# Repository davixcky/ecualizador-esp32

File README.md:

# Ecualizador de audio de tres bandas con ESP32

## Prototipo en protoboard

[Guía de montaje y esquema (PDF)](docs/protoboard/guia-prototipo-protoboard.pdf) · [Lista de materiales (CSV)](docs/protoboard/materiales.csv) · [Conexiones pin por pin (CSV)](docs/protoboard/conexiones.csv). Incluye pruebas con generador y osciloscopio, y ampliación con ESP32, pantalla y NeoPixel. [Fuente LaTeX](docs/latex/prototipo-protoboard.tex).

## Modelo mecánico vigente E.5

[Vista cerrada](hardware/E5-perforadas/3d/ecualizador-E5-cerrado.png) ·
[vista abierta](hardware/E5-perforadas/3d/ecualizador-E5-abierto.png) ·
[planta desplegada](hardware/E5-perforadas/3d/ecualizador-E5-planta.png) ·
[soporte de pantalla](hardware/E5-perforadas/3d/ecualizador-E5-pantalla-soporte-explotado.png) ·
[cómo regenerar](hardware/E5-perforadas/3d/README.md) ·
[prácticas propias de E.5](hardware/E5-perforadas/3d/BEST-PRACTICES.md).
Estas imágenes fijas son la referencia visual del CAD vigente: tapa magnética, piezas por encastre,
cinco controles rotativos, pantalla ESP32-3248S035 de 3,5" recibida (en vertical) y cuatro tarjetas perforadas.

El [video de 50 segundos](docs/video/ecualizador-animado.mp4) se conserva como material histórico.
Su [revisión](docs/video/REVIEW.md) documenta que el interior quedó anterior a los encastres actuales;
no debe usarse como guía de fabricación o montaje.

> **Controles vigentes:** no hay potenciómetros deslizables. Los informes y la presentación de la Fase 2 (`docs/latex/`, `docs/informe-fase2.*`, `docs/presentacion/`) y la carpeta [`cad/`](cad/LEEME-ARCHIVO.md) describen la revisión D.2 archivada, que sí los dibujaba; no representan el hardware que se va a montar. Las compras respaldadas están en [`hardware/COMPONENTES-COMPRADOS-VERIFICADOS.md`](hardware/COMPONENTES-COMPRADOS-VERIFICADOS.md).

Proyecto de Electrónica II · Universidad de la Costa · Leo Rojas, David Orozco y Manuel Castilla.

La ruta de audio usa filtros activos y controles analógicos. El firmware existente lee los niveles y dibuja una FFT para la pantalla Waveshare de **1,9 pulgadas, 170 × 320, ST7789V2**. El CAD vigente (2026-11-24) la sustituye por la **ESP32-3248S035 recibida** (TFT táctil ST7796 de 3,5 pulgadas, 320 × 480, en vertical; ya funciona con `firmware-cyd`), enlazada por **ESP-NOW** (solo recibe +5 V y GND por cable), y cambia el ESP32S de 38 pines por un **ESP32 DevKit V1 de 30 pines** (sin comprar). [`firmware-lilygo/`](firmware-lilygo/) contiene el simulador visual de la T4-S3 descartada (queda como referencia; no corresponde al CAD vigente). El gabinete E.5 mide 278 × 192 × 64 mm, usa cierre magnético y tres barras de luz (12 píxeles lógicos); el gabinete EQ / 03 con imanes de la Fase 2 quedó archivado.

| Entrega | Archivos actuales |
|---|---|
| Presentación en LaTeX | [PDF](docs/presentacion/presentacion-fase2.pdf) · [PowerPoint con notas](docs/presentacion/presentacion-fase2.pptx) · [PDF con notas](docs/presentacion/presentacion-notas.pdf) |
| Exposición con animaciones | [PowerPoint animado](docs/presentacion/presentacion-animada.pptx) · [PDF por pasos](docs/presentacion/presentacion-animada.pdf) · [Cómo presentar](docs/presentacion/LEEME.md) |
| Informe | [PDF](docs/informe-fase2.pdf) · [Word](docs/informe-fase2.docx) · [Markdown](docs/informe-fase2.md) |
| Fuentes editables en LaTeX | [Informe](docs/latex/informe.tex) · [Presentación Beamer](docs/latex/presentacion.tex) |
| Presentación corta de filtros | [PDF de 10 diapositivas](docs/presentacion/presentacion-filtros-hoy.pdf) · [PowerPoint con notas](docs/presentacion/presentacion-filtros-hoy.pptx) · [Fuente LaTeX](docs/latex/presentacion-filtros.tex) |
| Ensayo de hoy | [Generador y osciloscopio: guía](simulacion/velxio/DEMO-HOY.md) |
| Paquete para otro computador | [ZIP portátil: presentación, esquema y simulaciones](docs/exposicion-portable.zip) |
| Simulación en Velxio | [Abrir casos locales](simulacion/velxio/index.html) · [Instrucciones y alcance](simulacion/velxio/README.md) · [100 Hz](simulacion/velxio/filtros-100Hz.vlx) · [1 kHz](simulacion/velxio/filtros-1000Hz.vlx) · [8 kHz](simulacion/velxio/filtros-8000Hz.vlx) |
| Proyecto único E.4-LM324 | [Abrir en KiCad](hardware/E4-LM324/proyecto/ecualizador-E4-LM324.kicad_pro) · [Esquema PDF](hardware/E4-LM324/proyecto/ecualizador-E4-LM324.pdf) · [Fabricación](hardware/E4-LM324/fabricacion/) · [Vista superior](hardware/E4-LM324/vistas/3d-top.png) · [Vista inferior](hardware/E4-LM324/vistas/3d-bottom.png) · [Montaje](hardware/E4-LM324/README.md) |
| Prototipo modular E.5 en tarjetas perforadas | [Esquema modular PDF](hardware/E5-perforadas/esquema-modular-perforadas.pdf) · [Proyecto KiCad](hardware/E5-perforadas/proyecto/ecualizador-perforadas.kicad_pro) · [Conexiones](hardware/E5-perforadas/conexiones-entre-tarjetas.csv) · [Modelo 3D editable](hardware/E5-perforadas/3d/ecualizador-E5-perforadas.FCStd) · [Vista cerrada](hardware/E5-perforadas/3d/ecualizador-E5-cerrado.png) · [Vista abierta](hardware/E5-perforadas/3d/ecualizador-E5-abierto.png) · [Planta desplegada](hardware/E5-perforadas/3d/ecualizador-E5-planta.png) · [Modelo 3D: cómo regenerar](hardware/E5-perforadas/3d/README.md) · [Guía](hardware/E5-perforadas/README.md) |
| PCB E.3-LM324 de una cara | [KiCad](hardware/E3-LM324/placa/ecualizador-E3-LM324.kicad_pcb) · [Fabricación](hardware/E3-LM324/fabricacion/) · [Vista superior](hardware/E3-LM324/vistas/3d-top.png) · [Vista inferior](hardware/E3-LM324/vistas/3d-bottom.png) · [Reglas y montaje](hardware/E3-LM324/README.md) |
| PCB de una cara D.2 (anterior, MCP6004) | [Plano PDF](hardware/pcb-rev-D2.pdf) · [KiCad](hardware/ecualizador.kicad_pcb) · [DRC](hardware/drc.rpt) · [Montaje y puentes](hardware/una-cara/LEEME.md) · [BOM](hardware/fabricacion/bom.csv) |
| Modelos 3D | [Gabinete STEP](cad/ecualizador-gabinete.step) · [Piezas STL](cad/stl/) · [Retrofit D.3 STEP](hardware/3d/ecualizador-D3-retrofit.step) · [Vista superior](hardware/3d/ecualizador-D3-retrofit.png) · [Vista inferior](hardware/3d/ecualizador-D3-retrofit-inferior.png) · [PCB D.2 STEP](hardware/3d/ecualizador-placa.step) |
| Propuesta original y rúbrica | [Fase 1](docs/fase1/) |

## Estado de la revisión del 5 de noviembre de 2026

- **Actualización del 24 de noviembre de 2026:** la pantalla pasa de la LilyGO T4-S3 a la **ESP32-3248S035 de 3,5 pulgadas RECIBIDA** (la publicación anunciaba una de 2,8): montada en vertical, ST7796 confirmado y la interfaz de `firmware-cyd` ya corre en ella con vistas de bandas y espectro. Los datos viajarán por **ESP-NOW** (decisión del usuario); el arnés queda en +5 V/GND. El ESP32 del montaje pasa a un DevKit V1 de 30 pines (sin comprar; pines verificados compatibles). El modelo 3D E.5, sus 13 probetas y las camas de impresión reflejan la pantalla de 3,5; el video y el esquema eléctrico siguen mostrando revisiones anteriores.
- E.4-LM324 es la fuente única de fabricación: esquema físico y PCB en el mismo proyecto, paridad estricta KiCad con 0 diferencias, ERC con 0 errores y DRC con 0 errores/0 conexiones abiertas. Los 23 avisos ERC son exclusivamente pines `NC-*` intencionales.
- D.3 usa cuatro LM324N a 5 V, conserva VREF en 1,65 V y protege las cuatro entradas ADC con atenuadores 2:1 referidos a VREF. El firmware reconstruye la amplitud original.
- ngspice: 25 casos del diseño revisado cumplen; el caso histórico de Fase 1 se conserva deliberadamente como no conforme. El modelo funcional del LM324 valida margen de modo común, dinámica y protección ADC, pero no sustituye mediciones físicas.
- La PCB D.2 archivada conserva el ruteo y BOM del MCP6004 a 3,3 V. No coincide directamente con D.3: para reutilizarla se debe seguir la [adaptación LM324](hardware/RETROFIT-LM324.md). No enviar D.2 a fabricar como si ya incorporara R33–R40.
- La nueva PCB [E.3-LM324](hardware/E3-LM324/README.md) incorpora LM324 a 5 V y R33–R40: una cara, 23 alambres, pistas de 0,7 mm o más, donas de 1,9 mm o más y ninguna pista de paso entre pines a 2,54 mm. DRC sin errores ni conexiones abiertas; montaje físico pendiente.
- E.4 sustituye a E.3 como opción recomendada para soldadura manual: pads de componentes ovalados de al menos 2,4 × 2,0 mm, pads propios de puente de 2,4 mm, 25 alambres de hasta 30,9 mm, alimentación +5 V perimetral y ningún puente reutiliza un agujero de componente.
- Velxio: tres proyectos ejecutados con motor SPICE; predominan graves a 100 Hz, medios a 1 kHz y agudos a 8 kHz. Los filtros usan operacionales ideales. Un cuarto [ensayo animado de 12 NeoPixel](simulacion/velxio/led-animado.vlx) ejecuta código del ESP32; usa un patrón programado sin audio.
- Velxio integrado: entrada → filtros → detectores → ADC ESP32 → TFT ILI9341, usando QEMU. Se comprueba el predominio de cada banda con 100 Hz, 1 kHz y 8 kHz. FFT sin calibración de frecuencia; no incluye potencia ni adaptación LED. [Guía y modelos](simulacion/velxio/INTEGRADO.md).
- Firmware: compilación ESP32 correcta; 19 comprobaciones DSP y cinco comparaciones de dibujo por franjas correctas en el computador.
- El montaje físico, las mediciones con instrumentos y el requisito de más del 70 % de dispositivos adquiridos y conectados **siguen sin evidencia en este repositorio**.

Los [resultados ngspice vigentes](simulacion/resultados.md) corresponden a D.3-LM324; `docs/validacion/` conserva registros históricos de D.2. Los renders provienen del CAD y de KiCad; las pantallas se dibujan con el código de interfaz y datos de ejemplo.

## Pantalla e iluminación

J4 es un adaptador de ocho señales a 2,54 mm, no la huella GH1.25 de Waveshare. Conectar por **nombre de señal**, siguiendo la tabla del informe: VCC, GND, DIN, CLK, CS, DC, RST y BL. La interfaz trabaja en horizontal a 320 × 170.

GPIO25 controla la tira mediante un 74AHCT125 y 330 Ω. J5 lleva 5 V, DIN y GND. Se prevén dos tramos de 100 mm, seis LED por tramo, y canales de 102 × 10,6 × 3 mm con difusores. El brillo inicial es 32/255, fijo. La fuente prevista es de 5 V / 3 A por J6; **desconectar VBUS del USB cuando se usa esa fuente**. No alimentar los LED desde 3,3 V ni usar VREF como retorno.

## Reproducir los archivos

Los PDF usan el logo oficial CUC, rojo institucional y Red Hat Display, según el [manual consultado](img/marca/README.md). Las fuentes vigentes son los `.tex` (LuaLaTeX). El PowerPoint contiene imágenes de las diapositivas y notas; el texto se edita en LaTeX. El HTML anterior está archivado en `docs/archivo/`.

```sh
# TeX Live: latex-extra, lang-spanish, fonts-recommended, luatex; pandoc
# Python: pymupdf, python-pptx (para exportar PNG y PowerPoint)
bash herramientas/compilar_documentos.sh

# Firmware y pruebas en computador
pio run -d firmware
make -C firmware/test prueba pantallas

# Conectividad y simulación (ngspice, numpy, matplotlib)
python3 herramientas/verificar_netlist.py
.venv/bin/python herramientas/simulacion.py

# PCB de una cara: regenerar el esquema físico E.4 y verificar
python3 herramientas/generar_esquematico_e4.py
kicad-cli pcb drc --schematic-parity hardware/E4-LM324/proyecto/ecualizador-E4-LM324.kicad_pcb
python3 herramientas/validar_pcb_cnc.py hardware/E4-LM324/proyecto/ecualizador-E4-LM324.kicad_pcb 0.7 1.9

# CAD (CadQuery) y renders (Blender, KiCad)
.venv/bin/python herramientas/validar_cad.py
bash cad/generar.sh

# Repetir la comprobación web (Node y Playwright con Chromium)
node herramientas/validar_velxio.cjs
node herramientas/validar_led_velxio.cjs
```

Las vistas de ensamblaje y colores de bandas parten de C2-ABPR; la revisión EQ / 03 adopta acabado grafito, rotulación compacta y cierre magnético. Las cotas de pantalla, controles y conectores deben contrastarse con las piezas adquiridas antes de imprimir y montar.

La presentación incluye fragmentos del esquema real para explicar preamplificador, Sallen-Key, sumador y detector. Los PDF adjuntan el esquema, el plano D.2 y los proyectos Velxio. El enlace y el QR abren el editor; después se importa el caso `.vlx`. Ver [cierre magnético y cotas](cad/CIERRE-MAGNETICO.md).

La PCB D.2 organiza las etapas con el flujo Python/KiCad y Freerouting de medidor-energia-esp32: ESP32 a la derecha, operacionales por etapas y cableado identificado por colores. Usa una sola cara de cobre y puentes aislados. Los controles van en el panel y requieren las [cabeceras y cables de montaje](hardware/una-cara/LEEME.md). Los Gerbers de dos capas B.1 están archivados y no corresponden al montaje vigente.

### Placa única E.2 (propuesta, 33 alambres)

[E.2](hardware/E2-placa-unica/README.md) reduce los 80 tramos de D.2 a 33 alambres en una sola placa de una cara de 200 × 120 mm para el gabinete original. Usa plano de GND, componentes con las patas más abiertas para pasar pistas por debajo, y reasigna las secciones de los amplificadores y los GPIO. El firmware se compila con `pio run -e e2`. La alternativa de tres placas está en [E.1](hardware/E1-tres-placas/README.md).

### Montaje de los puentes

La cara superior lleva 29 puentes cortos (hasta 20 mm entre extremos). Los 51 cables restantes se montan aislados por debajo. El total sigue siendo 80 tramos; no se añade una capa de cobre. [La guía](hardware/PUENTES.md) y [el plano de cuatro páginas](hardware/pcb-rev-D2.pdf) indican la cara de cada conexión. Los arcos del render son orientativos: el montaje requiere comprobar separación, sujeción y continuidad.

### Prototipo de laboratorio con TL072CP (±12 V)

Para el montaje con los integrados disponibles: [guía PDF](docs/prototipo-tl072/guia-prototipo-TL072.pdf), [fuente LaTeX](docs/latex/prototipo-tl072.tex) y [paquete de conexiones y simulación](docs/prototipo-tl072/prototipo-TL072.zip). Utiliza cuatro TL072, salida de línea y medidas a 100 Hz, 1 kHz y 8 kHz. Es una variante analógica independiente del diseño MCP6004 de 3,3 V; sus salidas no se conectan directamente al ESP32.

Esquema completo del prototipo en una lámina A2: [PDF](docs/prototipo-tl072/esquema-completo-TL072.pdf) · [SVG editable](docs/prototipo-tl072/esquema-completo.svg). Incluido al final de la guía TL072.

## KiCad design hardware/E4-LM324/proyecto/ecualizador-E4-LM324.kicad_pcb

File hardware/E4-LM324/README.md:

# E.4-LM324 · una cara para soldadura manual

E.4 conserva el circuito validado D.3-LM324 y la topología de una sola cara, pero revisa la geometría pensando en fresado CNC y montaje con cautín. Es la revisión recomendada frente a E.3.

## Cambios para facilitar el montaje

- Todos los pads de componentes tienen al menos **2,4 × 2,0 mm**. En piezas sin restricción de paso, 132 pads son de 2,4 mm o mayores en ambos ejes.
- Los 44 pads propios de puentes son circulares de **2,4 mm**, con taladro de 0,8 mm.
- **Ningún puente reutiliza el agujero de un componente.** Cada extremo termina en un pad perforado propio; la comprobación automática aparece como `shared_bridge_holes: []`.
- El taladro propio de JP19 queda bajo el cuerpo de R25 por la isla de masa aislada de esa zona. Se suelda JP19 antes de montar R25; el agujero sigue siendo independiente de los dos pads de R25.
- El enlace largo de +5 V se sustituyó por una pista perimetral de 1,0 mm.
- No quedan ramales de cobre sueltos.

## Resultado verificado

| Regla | Resultado |
|---|---:|
| Cobre | solo B.Cu |
| Pista de señal mínima | 0,7 mm |
| Alimentación | 1,0 mm |
| Pad de componente mínimo real | 2,0 mm; eje largo ≥ 2,4 mm |
| Pad propio de puente | 2,4 mm |
| Vías metalizadas | 0 |
| Pistas de paso entre pines de 2,54 mm | 0 |
| Alambres | 25 |
| Longitud de alambre | mediana 13,8 mm; máximo 30,9 mm |
| KiCad DRC | 0 errores, 0 conexiones abiertas, 0 pistas colgantes |
| Paridad esquema ↔ PCB | 0 diferencias |
| ERC | 0 errores; 23 avisos `NC-*` intencionales |

El único aviso geométrico de taladro es `pth_inside_courtyard` para JP19/R25: identifica el orden de montaje descrito arriba, no un agujero compartido. Los avisos de serigrafía representan las líneas que identifican los alambres y no afectan el Gerber B.Cu.

## Orden de soldadura

1. Instalar los 25 alambres siguiendo [`alambres.csv`](alambres.csv). Soldar JP19 antes de R25. Todos los extremos usan agujeros propios; no insertar un puente en el agujero de otro componente.
2. Para que el desacoplo sea realmente local, no montar C4–C7 y C25 en sus posiciones remotas del dibujo. Soldar por la cara inferior, con las patas lo más cortas posible:
   - C4 entre U1-4 (+5 V) y U1-11 (GND).
   - C5 entre U2-4 y U2-11.
   - C6 entre U3-4 y U3-11.
   - C7 entre U4-4 y U4-11.
   - C25 entre U6-14 (+5 V) y U6-12 (GND en la asignación E.4).
   Usar cerámicos de 100 nF y reservar unos 3 mm bajo la PCB. Los agujeros rotulados C4–C7/C25 quedan sin poblar; sus pistas pueden permanecer.
3. Soldar resistencias, diodos y los demás capacitores pequeños.
4. Instalar los zócalos DIP, conectores y el zócalo del ESP32.
5. Instalar electrolíticos y piezas altas.
6. Sin insertar los integrados, comprobar continuidad, ausencia de corto entre +5 V/GND y +3.3VA/GND, y tensiones de alimentación.

## Archivos

- [`proyecto/ecualizador-E4-LM324.kicad_pro`](proyecto/ecualizador-E4-LM324.kicad_pro): **fuente única de verdad**; abre esquema y PCB juntos.
- [`proyecto/ecualizador-E4-LM324.pdf`](proyecto/ecualizador-E4-LM324.pdf): esquema físico E.4 exportado.
- [`fabricacion/`](fabricacion/): Gerber B.Cu, contorno, taladros y planos PDF.
- [`vistas/3d-top.png`](vistas/3d-top.png) y [`vistas/3d-bottom.png`](vistas/3d-bottom.png): montaje y cobre.
- [`validacion-cnc.json`](validacion-cnc.json): reglas geométricas automáticas.
- [`etiquetas-conectores.csv`](etiquetas-conectores.csv): orden físico de conectores.

Falta fabricar y medir una muestra; la validación digital no reemplaza esa prueba.

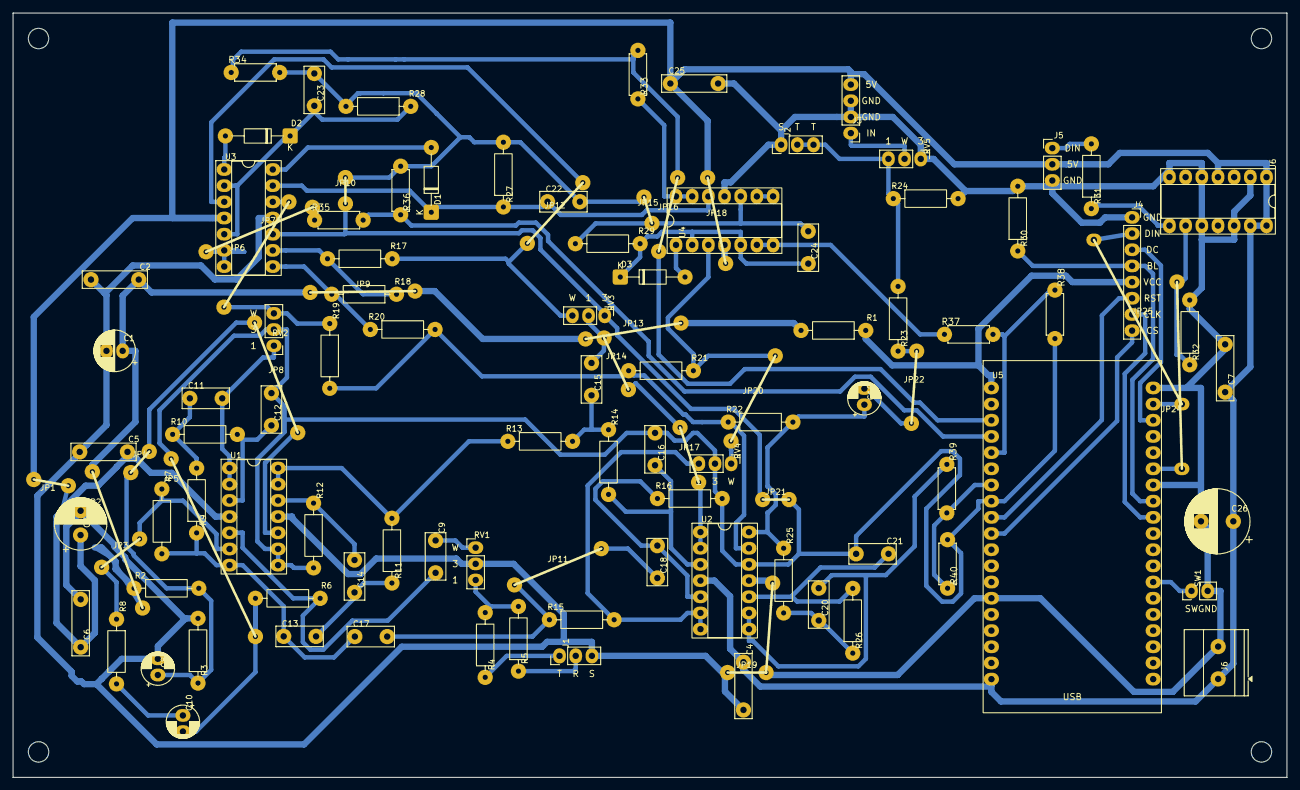
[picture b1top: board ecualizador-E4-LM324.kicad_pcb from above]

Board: 2 copper layers, 200.0 x 120.0 mm, 115 parts (0 on the bottom side), 63 nets.

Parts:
C1: 100u 10V; UnaCara_C1
C2, C4, C5, C6, C7, C25: 100n; C_Rect_L10.0mm_W2.5mm_P7.50mm_MKS4
C3: 470u 10V; UnaCara_C3
C8: 10u 16V; UnaCara_C8
C9: 1u film; UnaCara_C9
C10: 10u 16V; UnaCara_C10
C11: 100n film; UnaCara_C11
C12: 47n film; UnaCara_C12
C13: 10n film; UnaCara_C13
C14: 10n film; UnaCara_C14
C15: 10n film; UnaCara_C15
C16: 4n7 film; UnaCara_C16
C17: 10n film; UnaCara_C17
C18: 10n film; UnaCara_C18
C19: 10u 16V; UnaCara_C19
C20: 4n7 film; UnaCara_C20
C21: 2n2 film; UnaCara_C21
C22: 100n film; UnaCara_C22
C23: 100n film; UnaCara_C23
C24: 100n film; UnaCara_C24
C26: 1000u 10V; UnaCara_C26
D1, D2, D3: 1N4148; D_DO-35_SOD27_P10.16mm_Horizontal
H1, H2, H3, H4: MountingHole_3.2mm_M3
J1: Entrada de línea 3,5 mm; UnaCara_J1
J2: Salida de línea 3,5 mm; UnaCara_J2
J3: PAM8403; UnaCara_J3
J4: Waveshare 1.9 ST7789V2; UnaCara_J4
J5: NeoPixel 5V DIN GND; UnaCara_J5
J6: Entrada 5V 3A; UnaCara_J6
JP1, JP2, JP3, JP4, JP5, JP6, JP7, JP8, JP9, JP10, JP11, JP12, JP13, JP14, JP15, JP16, JP17, JP18, JP19, JP20, JP21, JP22, JP24, JP25: puente; Puente_alambre
R1: 10; R_Axial_DIN0207_L6.3mm_D2.5mm_P10.16mm_Horizontal
R2, R3, R8, R9, R10, R13, R14, R25, R26: 10k 1%; R_Axial_DIN0207_L6.3mm_D2.5mm_P10.16mm_Horizontal
R4, R5, R30, R32: 10k; R_Axial_DIN0207_L6.3mm_D2.5mm_P10.16mm_Horizontal
R6: 100k; R_Axial_DIN0207_L6.3mm_D2.5mm_P10.16mm_Horizontal
R7: 22k 1%; R_Axial_DIN0207_L6.3mm_D2.5mm_P10.16mm_Horizontal
R11: 27k 1%; R_Axial_DIN0207_L6.3mm_D2.5mm_P10.16mm_Horizontal
R12: 56k 1%; R_Axial_DIN0207_L6.3mm_D2.5mm_P10.16mm_Horizontal
R15: 2k7 1%; R_Axial_DIN0207_L6.3mm_D2.5mm_P10.16mm_Horizontal
R16: 5k6 1%; R_Axial_DIN0207_L6.3mm_D2.5mm_P10.16mm_Horizontal
R17, R18, R19, R20, R21: 47k 1%; R_Axial_DIN0207_L6.3mm_D2.5mm_P10.16mm_Horizontal
R22: 100k 1%; R_Axial_DIN0207_L6.3mm_D2.5mm_P10.16mm_Horizontal
R23: 100; R_Axial_DIN0207_L6.3mm_D2.5mm_P10.16mm_Horizontal
R24: 47k; R_Axial_DIN0207_L6.3mm_D2.5mm_P10.16mm_Horizontal
R27, R28, R29: 220k; R_Axial_DIN0207_L6.3mm_D2.5mm_P10.16mm_Horizontal
R31: 330; R_Axial_DIN0207_L6.3mm_D2.5mm_P10.16mm_Horizontal
R33, R34, R35, R36, R37, R38, R39, R40: 10k 1%; R_Axial_DIN0207_L6.3mm_D2.5mm_P7.62mm_Horizontal
RV1: 10k log; UnaCara_RV1
RV2: 10k lin; UnaCara_RV2
RV3: 10k lin; UnaCara_RV3
RV4: 10k lin; UnaCara_RV4
RV5: 10k log; UnaCara_RV5
SW1: Pulsador; UnaCara_SW1
U1: LM324N; UnaCara_U1
U2: LM324N; UnaCara_U2
U3: LM324N; UnaCara_U3
U4: LM324N; UnaCara_U4
U5: ESP32-DevKitC V4; UnaCara_U5
U6: 74AHCT125; UnaCara_U6

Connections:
+3.3VA: C1.1, C2.1, JP2.1, JP9.1, JP13.1, R1.2, R2.1
+3V3: J4.5, R1.1, U5.1
+5V: C3.1, C4.1, C5.1, C6.1, C7.1, C25.1, C26.1, J3.4, J5.2, J6.1, JP1.1, JP18.1, U1.4, U2.4, U3.4, U4.4, U5.19, U6.1, U6.4, U6.13, U6.14
/ADC_A: R37.2, R38.1, U5.5
/ADC_A_RAW: R37.1, U4.6, U4.7
/ADC_FFT: R39.2, R40.1, U5.7
/ADC_FFT_RAW: C20.2, R39.1, U2.8, U2.9
/ADC_G: JP16.1, R33.2, R34.1, U5.3
/ADC_G_RAW: R33.1, U4.13, U4.14
/ADC_M: R35.2, R36.1, U5.4
/ADC_M_RAW: JP7.1, R35.1, U3.6, U3.7
/AGUDOS: R15.2, RV4.3, U2.6, U2.7
/AMP_IN: J3.1, RV5.2
/A_W: JP20.1, R21.1, RV4.1, U4.3
/BTN: SW1.1, U5.32
/EQ_OUT: C19.1, R22.2, R25.1, U2.14
/GRAVES: C11.2, RV2.1, U1.1, U1.2
/G_W: JP6.1, R19.1, RV2.3, U3.12
/IN_L: J1.T, R4.1
/IN_R: J1.R, R5.1
/LED_5V: R31.1, U6.8
/LED_DATA: JP24.1, R32.1, U5.25, U6.9
/LED_DIN: J5.1, R31.2
/LINEA: J2.R, J2.S, R23.2, R24.1, RV5.3
/MEDIOS: C15.2, JP14.1, JP17.1, RV3.2, U2.1, U2.2
/MED_HP: R11.2, R13.1, U1.13, U1.14
/MIX: R4.2, R5.2, RV1.3
/M_INV: R18.2, R20.1, U3.8
/M_W: JP12.1, R17.1, RV3.3, U3.3
/NIVEL: C9.1, RV1.1
/PRE: C13.1, C17.1, R7.2, R9.1, U1.7
/TFT_BL: J4.4, R30.1, U5.27
/TFT_CS: J4.8, U5.10
/TFT_DC: J4.3, U5.22
/TFT_MOSI: J4.2, JP25.1, U5.21
/TFT_RST: J4.6, U5.9
/TFT_SCK: J4.7, U5.28
/VREF: C10.2, C12.2, C16.2, C21.2, C22.2, C23.2, C24.2, JP5.1, JP10.1, JP15.1, JP21.1, R6.2, R12.2, R16.2, R27.2, R28.2, R29.2, R34.2, R36.2, R38.2, R40.2, RV2.2, RV3.1, RV4.2, U1.8, U1.9, U2.12, U3.10, U4.10, U5.8
GND: C1.2, C2.2, C3.2, C4.2, C5.2, C6.2, C7.2, C8.2, C25.2, C26.2, J1.S, J2.T, J3.2, J3.3, J4.1, J5.3, J6.2, JP19.1, R3.2, R24.2, R30.2, R32.2, RV1.2, RV5.1, SW1.2, U1.11, U2.11, U3.11, U4.11, U5.14, U5.20, U5.26, U6.2, U6.5, U6.7, U6.10, U6.12
unnamed: C10.1, R8.2
unnamed: C11.1, R9.2, R10.1
unnamed: C13.2, C14.1, R11.1
unnamed: C15.1, R13.2, R14.1
unnamed: C17.2, C18.1, JP11.1, R15.1
unnamed: C19.2, JP22.1, R23.1
unnamed: C20.1, R25.2, R26.1
unnamed: D1.2, U3.14
unnamed: C22.1, D1.1, R27.1, U3.13, U4.12
unnamed: D2.2, U3.1
unnamed: C23.1, D2.1, R28.1, U3.2, U3.5
unnamed: D3.2, U4.1
unnamed: C24.1, D3.1, R29.1, U4.2, U4.5
unnamed: C12.1, R10.2, U1.3
unnamed: C9.2, R6.1, U1.5
unnamed: JP3.1, R7.1, R8.1, U1.6
unnamed: C8.1, JP4.1, JP8.1, R2.2, R3.1, U1.10
unnamed: C14.2, R12.1, U1.12
unnamed: C16.1, R14.2, U2.3
unnamed: C18.2, R16.1, U2.5
unnamed: C21.1, R26.2, U2.10
unnamed: R19.2, R20.2, R21.2, R22.1, U2.13
unnamed: R17.2, R18.1, U3.9
unnamed: U4.8, U4.9

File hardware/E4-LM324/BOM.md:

| # | Referencias | Descripción | Valor | Cant. |
|---:|---|---|---|---:|
| 1 | U1 | Amplificador operacional cuádruple LM324N (DIP-14) + zócalo | — | 1 |
| 2 | U2 | Amplificador operacional cuádruple LM324N (DIP-14) + zócalo | — | 1 |
| 3 | U3 | Amplificador operacional cuádruple LM324N (DIP-14) + zócalo | — | 1 |
| 4 | U4 | Amplificador operacional cuádruple LM324N (DIP-14) + zócalo | — | 1 |
| 5 | U6 | Adaptador lógico cuádruple 74AHCT125 (DIP-14) | — | 1 |
| 6 | U5 | Tarjeta ESP32-DevKitC V4 (38 pines) + 2 zócalos hembra 1 × 19 | — | 1 |
| 7 | R1 | Resistencia de película metálica 1/4 W | 10 | 1 |
| 8 | R23 | Resistencia de película metálica 1/4 W | 100 | 1 |
| 9 | R6 | Resistencia de película metálica 1/4 W | 100k | 1 |
| 10 | R22 | Resistencia de película metálica 1/4 W | 100k 1% | 1 |
| 11 | R4 | Resistencia de película metálica 1/4 W | 10k | 1 |
| 12 | R5 | Resistencia de película metálica 1/4 W | 10k | 1 |
| 13 | R30 | Resistencia de película metálica 1/4 W | 10k | 1 |
| 14 | R32 | Resistencia de película metálica 1/4 W | 10k | 1 |
| 15 | R2 | Resistencia de película metálica 1/4 W | 10k 1% | 1 |
| 16 | R3 | Resistencia de película metálica 1/4 W | 10k 1% | 1 |
| 17 | R8 | Resistencia de película metálica 1/4 W | 10k 1% | 1 |
| 18 | R9 | Resistencia de película metálica 1/4 W | 10k 1% | 1 |
| 19 | R10 | Resistencia de película metálica 1/4 W | 10k 1% | 1 |
| 20 | R13 | Resistencia de película metálica 1/4 W | 10k 1% | 1 |
| 21 | R14 | Resistencia de película metálica 1/4 W | 10k 1% | 1 |
| 22 | R25 | Resistencia de película metálica 1/4 W | 10k 1% | 1 |
| 23 | R26 | Resistencia de película metálica 1/4 W | 10k 1% | 1 |
| 24 | R33–R40 | Resistencia de película metálica 1/4 W | 10k 1% | 8 |
| 25 | R27 | Resistencia de película metálica 1/4 W | 220k | 1 |
| 26 | R28 | Resistencia de película metálica 1/4 W | 220k | 1 |
| 27 | R29 | Resistencia de película metálica 1/4 W | 220k | 1 |
| 28 | R7 | Resistencia de película metálica 1/4 W | 22k 1% | 1 |
| 29 | R11 | Resistencia de película metálica 1/4 W | 27k 1% | 1 |
| 30 | R15 | Resistencia de película metálica 1/4 W | 2k7 1% | 1 |
| 31 | R31 | Resistencia de película metálica 1/4 W | 330 | 1 |
| 32 | R24 | Resistencia de película metálica 1/4 W | 47k | 1 |
| 33 | R17 | Resistencia de película metálica 1/4 W | 47k 1% | 1 |
| 34 | R18 | Resistencia de película metálica 1/4 W | 47k 1% | 1 |
| 35 | R19 | Resistencia de película metálica 1/4 W | 47k 1% | 1 |
| 36 | R20 | Resistencia de película metálica 1/4 W | 47k 1% | 1 |
| 37 | R21 | Resistencia de película metálica 1/4 W | 47k 1% | 1 |
| 38 | R12 | Resistencia de película metálica 1/4 W | 56k 1% | 1 |
| 39 | R16 | Resistencia de película metálica 1/4 W | 5k6 1% | 1 |
| 40 | C2 | Condensador cerámico | 100 n | 1 |
| 41 | C4 | Condensador cerámico | 100 n | 1 |
| 42 | C5 | Condensador cerámico | 100 n | 1 |
| 43 | C6 | Condensador cerámico | 100 n | 1 |
| 44 | C7 | Condensador cerámico | 100 n | 1 |
| 45 | C25 | Condensador cerámico | 100 n | 1 |
| 46 | C11 | Condensador de película (poliéster) | 100 n | 1 |
| 47 | C22 | Condensador de película (poliéster) | 100 n | 1 |
| 48 | C23 | Condensador de película (poliéster) | 100 n | 1 |
| 49 | C24 | Condensador de película (poliéster) | 100 n | 1 |
| 50 | C13 | Condensador de película (poliéster) | 10 n | 1 |
| 51 | C14 | Condensador de película (poliéster) | 10 n | 1 |
| 52 | C15 | Condensador de película (poliéster) | 10 n | 1 |
| 53 | C17 | Condensador de película (poliéster) | 10 n | 1 |
| 54 | C18 | Condensador de película (poliéster) | 10 n | 1 |
| 55 | C9 | Condensador de película (poliéster) | 1 µ | 1 |
| 56 | C21 | Condensador de película (poliéster) | 2 n2 | 1 |
| 57 | C12 | Condensador de película (poliéster) | 47 n | 1 |
| 58 | C16 | Condensador de película (poliéster) | 4 n7 | 1 |
| 59 | C20 | Condensador de película (poliéster) | 4 n7 | 1 |
| 60 | C26 | Condensador electrolítico | 1000 µ 10V | 1 |
| 61 | C1 | Condensador electrolítico | 100 µ 10V | 1 |
| 62 | C8 | Condensador electrolítico | 10 µ 16V | 1 |
| 63 | C10 | Condensador electrolítico | 10 µ 16V | 1 |
| 64 | C19 | Condensador electrolítico | 10 µ 16V | 1 |
| 65 | C3 | Condensador electrolítico | 470 µ 10V | 1 |
| 66 | RV2 | Potenciómetro rotativo 9 mm (Alps RK09K), eje 20 mm | 10k lin | 1 |
| 67 | RV3 | Potenciómetro rotativo 9 mm (Alps RK09K), eje 20 mm | 10k lin | 1 |
| 68 | RV4 | Potenciómetro rotativo 9 mm (Alps RK09K), eje 20 mm | 10k lin | 1 |
| 69 | RV1 | Potenciómetro rotativo 9 mm (Alps RK09K), eje 20 mm | 10k log | 1 |
| 70 | RV5 | Potenciómetro rotativo 9 mm (Alps RK09K), eje 20 mm | 10k log | 1 |
| 71 | D1 | Diodo de señal | 1N4148 | 1 |
| 72 | D2 | Diodo de señal | 1N4148 | 1 |
| 73 | D3 | Diodo de señal | 1N4148 | 1 |
| 74 | J1 | Jack hembra estéreo 3,5 mm para PCB | — | 1 |
| 75 | J2 | Jack hembra estéreo 3,5 mm para PCB | — | 1 |
| 76 | J6 | Bornera de alimentación 1 × 2 | — | 1 |
| 77 | J5 | Espadín macho 1 × 3 | — | 1 |
| 78 | J3 | Espadín macho 1 × 4 | — | 1 |
| 79 | J4 | Zócalo hembra 1 × 14 (pantalla) | — | 1 |
| 80 | SW1 | Pulsador táctil 6 × 6 mm (eje largo) | — | 1 |
| 81 | — | Tira WS2812B de 10 mm, 60 LED/m: dos tramos de 100 mm (12 LED) | — | 1 |
| 82 | — | Módulo amplificador PAM8403 (2 × 3 W, 5 V) | — | 1 |
| 83 | — | Parlante de 3 W, 4 Ω, 40–50 mm | — | 1 |
| 84 | — | Waveshare 1,9 pulgadas 170 × 320 SPI ST7789V2 | — | 1 |
| 85 | — | Perillas para potenciómetro de eje D y tapas para deslizable | — | 5 |
| 86 | — | Fuente regulada de 5 V, 3 A y cable USB sin VBUS | — | 1 |
| 87 | — | Cable de audio 3,5 mm macho-macho | — | 1 |

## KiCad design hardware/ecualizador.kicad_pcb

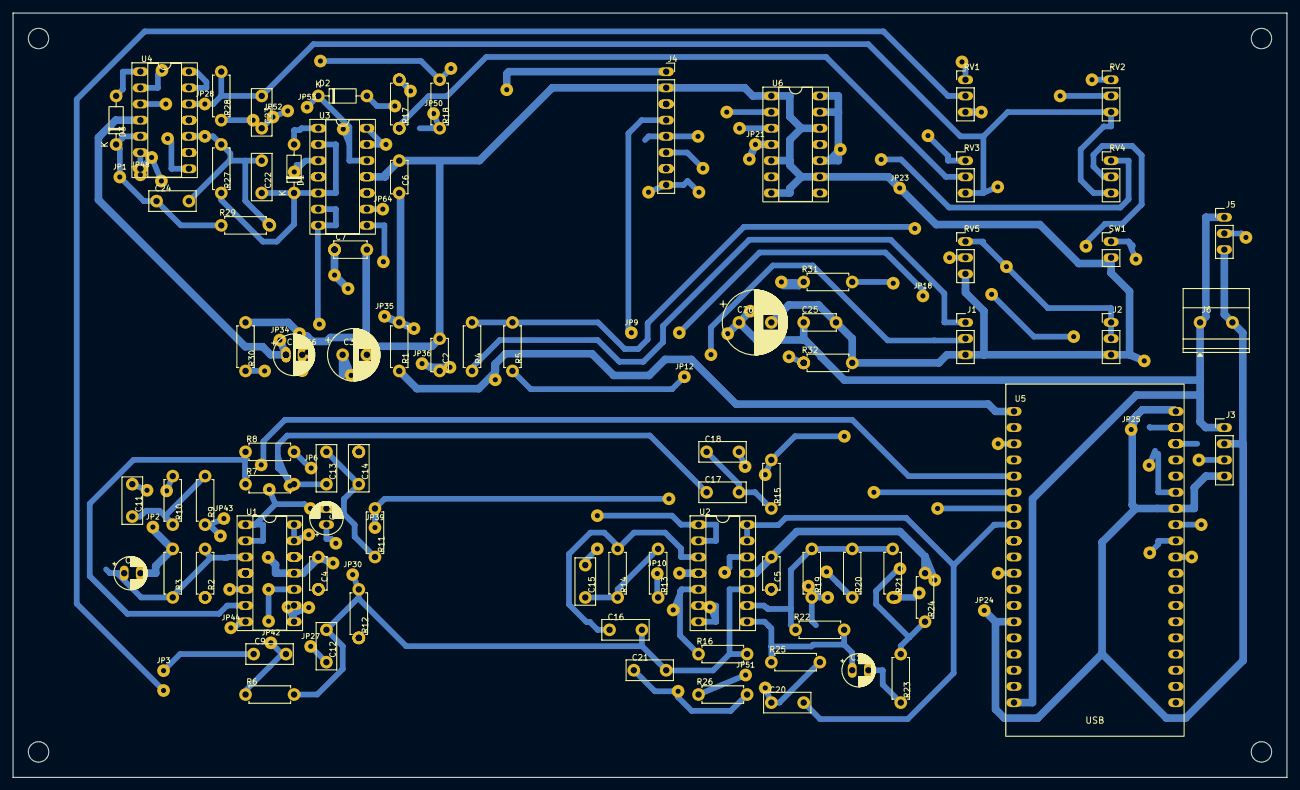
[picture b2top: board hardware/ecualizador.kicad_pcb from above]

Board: 2 copper layers, 200.0 x 120.0 mm, 162 parts (0 on the bottom side), 59 nets.

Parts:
C1: 100u 10V; UnaCara_C1
C2: 100n; UnaCara_C2
C3: 470u 10V; UnaCara_C3
C4: 100n; UnaCara_C4
C5: 100n; UnaCara_C5
C6: 100n; UnaCara_C6
C7: 100n; UnaCara_C7
C8: 10u 16V; UnaCara_C8
C9: 1u film; UnaCara_C9
C10: 10u 16V; UnaCara_C10
C11: 100n film; UnaCara_C11
C12: 47n film; UnaCara_C12
C13: 10n film; UnaCara_C13
C14: 10n film; UnaCara_C14
C15: 10n film; UnaCara_C15
C16: 4n7 film; UnaCara_C16
C17: 10n film; UnaCara_C17
C18: 10n film; UnaCara_C18
C19: 10u 16V; UnaCara_C19
C20: 4n7 film; UnaCara_C20
C21: 2n2 film; UnaCara_C21
C22: 100n film; UnaCara_C22
C23: 100n film; UnaCara_C23
C24: 100n film; UnaCara_C24
C25: 100n; UnaCara_C25
C26: 1000u 10V; UnaCara_C26
D1: 1N4148; UnaCara_D1
D2: 1N4148; UnaCara_D2
D3: 1N4148; UnaCara_D3
H1, H2, H3, H4: MountingHole_3.2mm_M3
J1: Entrada de línea 3,5 mm; UnaCara_J1
J2: Salida de línea 3,5 mm; UnaCara_J2
J3: PAM8403; UnaCara_J3
J4: Waveshare 1.9 ST7789V2; UnaCara_J4
J5: NeoPixel 5V DIN GND; UnaCara_J5
J6: Entrada 5V 3A; UnaCara_J6
JP1, JP2, JP3, JP4, JP5, JP6, JP7, JP8, JP9, JP10, JP11, JP12, JP13, JP14, JP15, JP16, JP17, JP18, JP19, JP20, JP21, JP22, JP23, JP24, JP25, JP26, JP27, JP28, JP29, JP30, JP31, JP32, JP33, JP34, JP35, JP36, JP37, JP38, JP39, JP40, JP41, JP42, JP43, JP44, JP45, JP46, JP47, JP48, JP49, JP50, JP51, JP52, JP53, JP54, JP55, JP56, JP57, JP58, JP59, JP60, JP61, JP62, JP63, JP64, JP65, JP66: Puente aislado
JP67, JP68, JP69, JP70, JP71, JP72, JP73, JP74, JP75, JP76, JP77, JP78, JP79: Puente a terminal
R1: 10; UnaCara_R1
R2: 10k 1%; UnaCara_R2
R3: 10k 1%; UnaCara_R3
R4: 10k; UnaCara_R4
R5: 10k; UnaCara_R5
R6: 100k; UnaCara_R6
R7: 22k 1%; UnaCara_R7
R8: 10k 1%; UnaCara_R8
R9: 10k 1%; UnaCara_R9
R10: 10k 1%; UnaCara_R10
R11: 27k 1%; UnaCara_R11
R12: 56k 1%; UnaCara_R12
R13: 10k 1%; UnaCara_R13
R14: 10k 1%; UnaCara_R14
R15: 2k7 1%; UnaCara_R15
R16: 5k6 1%; UnaCara_R16
R17: 47k 1%; UnaCara_R17
R18: 47k 1%; UnaCara_R18
R19: 47k 1%; UnaCara_R19
R20: 47k 1%; UnaCara_R20
R21: 47k 1%; UnaCara_R21
R22: 100k 1%; UnaCara_R22
R23: 100; UnaCara_R23
R24: 47k; UnaCara_R24
R25: 10k 1%; UnaCara_R25
R26: 10k 1%; UnaCara_R26
R27: 220k; UnaCara_R27
R28: 220k; UnaCara_R28
R29: 220k; UnaCara_R29
R30: 10k; UnaCara_R30
R31: 330; UnaCara_R31
R32: 10k; UnaCara_R32
RV1: 10k log; UnaCara_RV1
RV2: 10k lin; UnaCara_RV2
RV3: 10k lin; UnaCara_RV3
RV4: 10k lin; UnaCara_RV4
RV5: 10k log; UnaCara_RV5
SW1: Pulsador; UnaCara_SW1
U1: MCP6004; UnaCara_U1
U2: MCP6004; UnaCara_U2
U3: MCP6004; UnaCara_U3
U4: MCP6004; UnaCara_U4
U5: ESP32-DevKitC V4; UnaCara_U5
U6: 74AHCT125; UnaCara_U6

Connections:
+3.3VA: C1.1, C2.1, C4.1, C5.1, C6.1, C7.1, JP34.1, JP35.1, JP36.1, JP37.1, JP70.1, JP71.1, JP72.1, JP73.1, JP74.1, R1.2, R2.1, U1.4, U2.4, U3.4, U4.4
+3V3: J4.1, JP54.1, R1.1, U5.1
+5V: C3.1, C25.1, C26.1, J3.1, J5.1, J6.1, JP20.1, JP21.1, JP63.1, U5.19, U6.4, U6.10, U6.13, U6.14
/ADC_A: JP48.1, JP49.1, U4.6, U4.7, U5.7
/ADC_FFT: C20.2, U2.13, U2.14, U5.8
/ADC_G: JP5.1, U3.6, U3.7, U5.5
/ADC_M: JP60.1, U3.13, U3.14, U5.6
/AGUDOS: JP13.1, JP33.1, R15.2, RV4.1, U2.6, U2.7
/AMP_IN: J3.3, JP38.1, RV5.2
/A_W: JP17.1, JP40.1, R21.1, RV4.2, U4.3
/BTN: JP62.1, SW1.1, U5.11
/EQ_OUT: C19.1, R22.2, R25.1, U2.8
/GRAVES: C11.2, JP45.1, JP46.1, RV2.1, U1.8, U1.9
/G_W: JP59.1, JP65.1, R19.1, RV2.2, U3.3
/IN_L: J1.T, R4.1
/IN_R: J1.R, JP12.1, R5.1
/LED_5V: JP47.1, R31.1, U6.3
/LED_DATA: JP61.1, JP76.1, R32.1, U5.9, U6.2
/LED_DIN: J5.2, JP14.1, R31.2
/LINEA: J2.R, J2.T, JP15.1, R23.2, R24.1, RV5.1
/MEDIOS: C15.2, JP8.1, RV3.1, U2.1, U2.2
/MED_HP: JP10.1, JP39.1, R11.2, R13.1, U1.13, U1.14
/M_INV: JP4.1, JP32.1, R18.2, R20.1, U4.8
/M_W: JP77.1, R17.1, RV3.2, U3.10
/PRE: C13.1, C17.1, JP43.1, JP44.1, R7.2, R9.1, U1.7
/TFT_BL: J4.8, JP57.1, JP58.1, R30.1, U5.27
/TFT_CS: J4.5, JP55.1, U5.29
/TFT_DC: J4.6, JP56.1, U5.25
/TFT_MOSI: J4.3, JP78.1, U5.21
/TFT_RST: J4.7, JP79.1, U5.22
/TFT_SCK: J4.4, JP9.1, JP18.1, JP19.1, U5.28
/VREF: C10.2, C12.2, C16.2, C21.2, C22.2, C23.2, C24.2, JP28.1, JP29.1, JP30.1, JP31.1, R6.2, R12.2, R16.2, R27.2, R28.2, R29.2, RV2.3, RV3.3, RV4.3, U1.1, U1.2, U2.10, U4.10, U4.12, U5.3
GND: C1.2, C2.2, C3.2, C4.2, C5.2, C6.2, C7.2, C8.2, C25.2, C26.2, J1.S, J2.S, J3.2, J3.4, J4.2, J5.3, J6.2, JP2.1, JP22.1, JP23.1, JP24.1, JP25.1, JP66.1, JP67.1, R3.2, R24.2, R30.2, R32.2, RV1.3, RV5.3, SW1.2, U1.11, U2.11, U3.11, U4.11, U5.14, U5.20, U5.26, U6.1, U6.5, U6.7, U6.9, U6.12
unnamed: C9.1, JP3.1, RV1.2
unnamed: C10.1, JP6.1, R8.2
unnamed: C11.1, R9.2, R10.1
unnamed: C13.2, C14.1, R11.1
unnamed: C15.1, R13.2, R14.1
unnamed: C17.2, C18.1, R15.1
unnamed: C19.2, R23.1
unnamed: C20.1, JP51.1, R25.2, R26.1
unnamed: D1.2, U3.1
unnamed: C22.1, D1.1, R27.1, U3.2, U3.5
unnamed: D2.2, JP7.1, U3.8
unnamed: C23.1, D2.1, JP52.1, JP53.1, JP64.1, R28.1, U3.9, U3.12
unnamed: D3.2, U4.1
unnamed: C24.1, D3.1, JP1.1, R29.1, U4.2, U4.5
unnamed: JP16.1, R4.2, R5.2, RV1.1
unnamed: C8.1, R2.2, R3.1, U1.3
unnamed: C9.2, JP42.1, R6.1, U1.5
unnamed: R7.1, R8.1, U1.6
unnamed: C12.1, JP26.1, JP27.1, R10.2, U1.10
unnamed: C14.2, JP68.1, JP69.1, R12.1, U1.12
unnamed: C16.1, R14.2, U2.3
unnamed: C18.2, JP41.1, R16.1, U2.5
unnamed: R19.2, R20.2, R21.2, R22.1, U2.9
unnamed: C21.1, JP11.1, R26.2, U2.12
unnamed: JP50.1, JP75.1, R17.2, R18.1, U4.9
unnamed: U4.13, U4.14

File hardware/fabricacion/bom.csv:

"Reference","Value","Footprint","QUANTITY"
"C1","100u 10V","Ecualizador:UnaCara_C1","1"
"C2","100n","Ecualizador:UnaCara_C2","1"
"C3","470u 10V","Ecualizador:UnaCara_C3","1"
"C4","100n","Ecualizador:UnaCara_C4","1"
"C5","100n","Ecualizador:UnaCara_C5","1"
"C6","100n","Ecualizador:UnaCara_C6","1"
"C7","100n","Ecualizador:UnaCara_C7","1"
"C8","10u 16V","Ecualizador:UnaCara_C8","1"
"C9","1u film","Ecualizador:UnaCara_C9","1"
"C10","10u 16V","Ecualizador:UnaCara_C10","1"
"C11","100n film","Ecualizador:UnaCara_C11","1"
"C12","47n film","Ecualizador:UnaCara_C12","1"
"C13","10n film","Ecualizador:UnaCara_C13","1"
"C14","10n film","Ecualizador:UnaCara_C14","1"
"C15","10n film","Ecualizador:UnaCara_C15","1"
"C16","4n7 film","Ecualizador:UnaCara_C16","1"
"C17","10n film","Ecualizador:UnaCara_C17","1"
"C18","10n film","Ecualizador:UnaCara_C18","1"
"C19","10u 16V","Ecualizador:UnaCara_C19","1"
"C20","4n7 film","Ecualizador:UnaCara_C20","1"
"C21","2n2 film","Ecualizador:UnaCara_C21","1"
"C22","100n film","Ecualizador:UnaCara_C22","1"
"C23","100n film","Ecualizador:UnaCara_C23","1"
"C24","100n film","Ecualizador:UnaCara_C24","1"
"C25","100n","Ecualizador:UnaCara_C25","1"
"C26","1000u 10V","Ecualizador:UnaCara_C26","1"
"D1","1N4148","Ecualizador:UnaCara_D1","1"
"D2","1N4148","Ecualizador:UnaCara_D2","1"
"D3","1N4148","Ecualizador:UnaCara_D3","1"
"J1","Entrada de línea 3,5 mm","Ecualizador:UnaCara_J1","1"
"J2","Salida de línea 3,5 mm","Ecualizador:UnaCara_J2","1"
"J3","PAM8403","Ecualizador:UnaCara_J3","1"
"J4","Waveshare 1.9 ST7789V2","Ecualizador:UnaCara_J4","1"
"J5","NeoPixel 5V DIN GND","Ecualizador:UnaCara_J5","1"
"J6","Entrada 5V 3A","Ecualizador:UnaCara_J6","1"
"R1","10","Ecualizador:UnaCara_R1","1"
"R2","10k 1%","Ecualizador:UnaCara_R2","1"
"R3","10k 1%","Ecualizador:UnaCara_R3","1"
"R4","10k","Ecualizador:UnaCara_R4","1"
"R5","10k","Ecualizador:UnaCara_R5","1"
"R6","100k","Ecualizador:UnaCara_R6","1"
"R7","22k 1%","Ecualizador:UnaCara_R7","1"
"R8","10k 1%","Ecualizador:UnaCara_R8","1"
"R9","10k 1%","Ecualizador:UnaCara_R9","1"
"R10","10k 1%","Ecualizador:UnaCara_R10","1"
"R11","27k 1%","Ecualizador:UnaCara_R11","1"
"R12","56k 1%","Ecualizador:UnaCara_R12","1"
"R13","10k 1%","Ecualizador:UnaCara_R13","1"
"R14","10k 1%","Ecualizador:UnaCara_R14","1"
"R15","2k7 1%","Ecualizador:UnaCara_R15","1"
"R16","5k6 1%","Ecualizador:UnaCara_R16","1"
"R17","47k 1%","Ecualizador:UnaCara_R17","1"
"R18","47k 1%","Ecualizador:UnaCara_R18","1"
"R19","47k 1%","Ecualizador:UnaCara_R19","1"
"R20","47k 1%","Ecualizador:UnaCara_R20","1"
"R21","47k 1%","Ecualizador:UnaCara_R21","1"
"R22","100k 1%","Ecualizador:UnaCara_R22","1"
"R23","100","Ecualizador:UnaCara_R23","1"
"R24","47k","Ecualizador:UnaCara_R24","1"
"R25","10k 1%","Ecualizador:UnaCara_R25","1"
"R26","10k 1%","Ecualizador:UnaCara_R26","1"
"R27","220k","Ecualizador:UnaCara_R27","1"
"R28","220k","Ecualizador:UnaCara_R28","1"
"R29","220k","Ecualizador:UnaCara_R29","1"
"R30","10k","Ecualizador:UnaCara_R30","1"
"R31","330","Ecualizador:UnaCara_R31","1"
"R32","10k","Ecualizador:UnaCara_R32","1"
"RV1","10k log","Ecualizador:UnaCara_RV1","1"
"RV2","10k lin","Ecualizador:UnaCara_RV2","1"
"RV3","10k lin","Ecualizador:UnaCara_RV3","1"
"RV4","10k lin","Ecualizador:UnaCara_RV4","1"
"RV5","10k log","Ecualizador:UnaCara_RV5","1"
"SW1","Pulsador","Ecualizador:UnaCara_SW1","1"
"U1","MCP6004","Ecualizador:UnaCara_U1","1"
"U2","MCP6004","Ecualizador:UnaCara_U2","1"
"U3","MCP6004","Ecualizador:UnaCara_U3","1"
"U4","MCP6004","Ecualizador:UnaCara_U4","1"
"U5","ESP32-DevKitC V4","Ecualizador:UnaCara_U5","1"
"U6","74AHCT125","Ecualizador:UnaCara_U6","1"

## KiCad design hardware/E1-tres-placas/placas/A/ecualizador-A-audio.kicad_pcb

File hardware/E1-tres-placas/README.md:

# E.1 · Tres placas de una cara (alternativa)

El circuito de D.2 se reparte en tres placas CNC de una cara unidas por cables. Las tres pasan el DRC con 0 errores y 0 conexiones abiertas, y las netlists coinciden pin a pin con el esquema (59 redes).

| Placa | Tamaño (mm) | Puentes | Alambres directos | Total |
|---|---|---|---|---|
| A · audio | 110 × 78 | 21 | 9 | 30 |
| B · detectores | 70 × 55 | 5 | 4 | 9 |
| C · control | 100 × 75 | 5 | 0 | 5 |

En total son 44 alambres más los 15 cables entre placas de [`cables-entre-placas.csv`](cables-entre-placas.csv). Las tres placas necesitan un gabinete ampliado (220 × 143 mm por fuera), cuyas vistas están en `vistas/`.

Las placas se generan con `herramientas/tres_placas/`. Para la entrega se prefiere E.2: una sola placa, 33 alambres y el gabinete original.

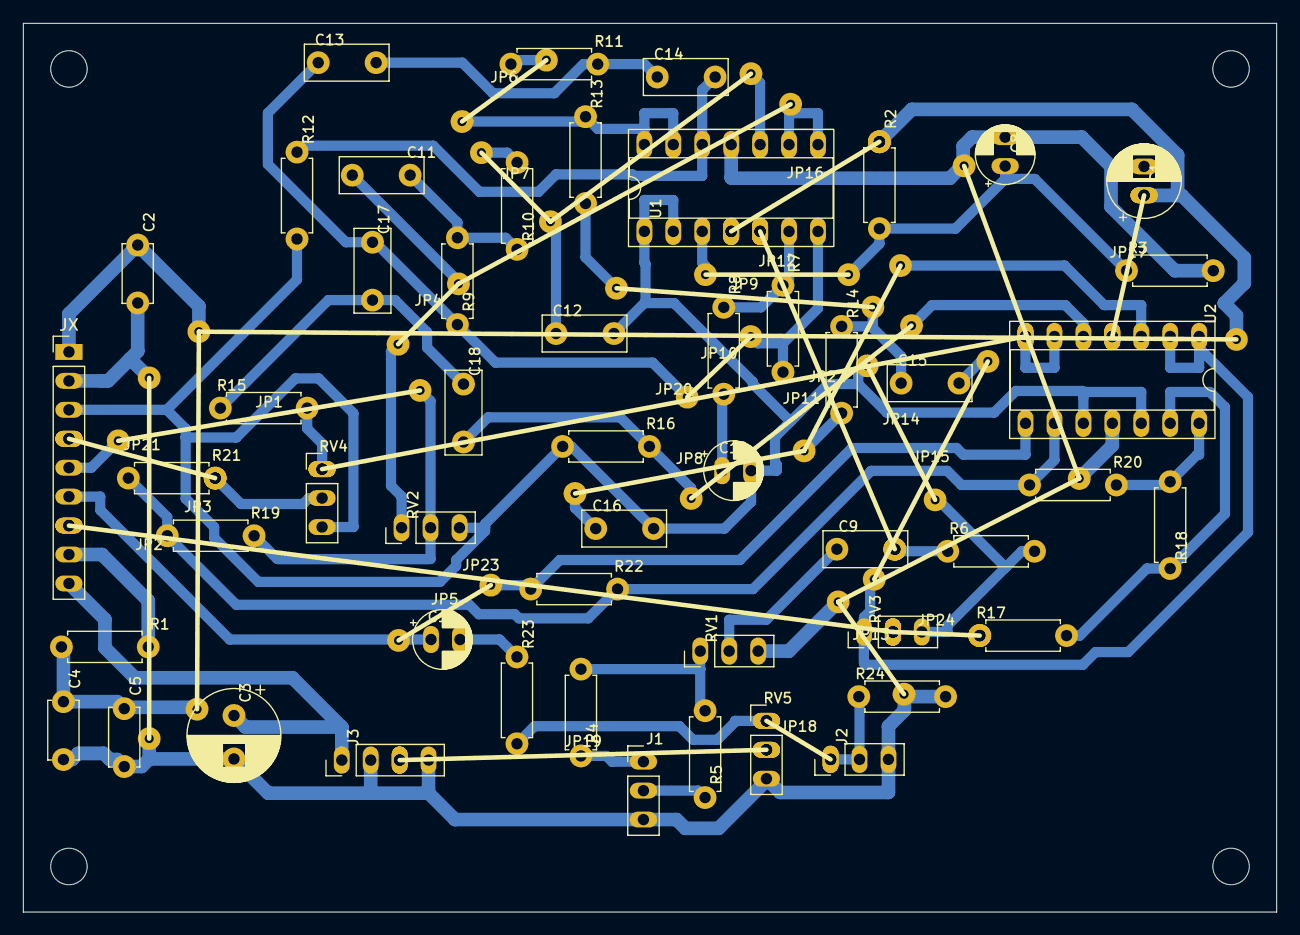
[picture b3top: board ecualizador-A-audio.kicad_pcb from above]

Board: 2 copper layers, 110.0 x 78.0 mm, 80 parts (0 on the bottom side), 36 nets.

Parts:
C1: 100u 10V; UnaCara_C1
C2: 100n; UnaCara_C2
C3: 470u 10V; UnaCara_C3
C4: 100n; UnaCara_C4
C5: 100n; UnaCara_C5
C8: 10u 16V; UnaCara_C8
C9: 1u film; UnaCara_C9
C10: 10u 16V; UnaCara_C10
C11: 100n film; UnaCara_C11
C12: 47n film; UnaCara_C12
C13: 10n film; UnaCara_C13
C14: 10n film; UnaCara_C14
C15: 10n film; UnaCara_C15
C16: 4n7 film; UnaCara_C16
C17: 10n film; UnaCara_C17
C18: 10n film; UnaCara_C18
C19: 10u 16V; UnaCara_C19
H1, H2, H3, H4: MountingHole_3.2mm_M3
J1: Entrada de línea 3,5 mm; UnaCara_J1
J2: Salida de línea 3,5 mm; UnaCara_J2
J3: PAM8403; UnaCara_J3
JP1, JP2, JP3, JP4, JP5, JP6, JP7, JP8, JP9, JP10, JP11, JP12, JP13, JP14, JP15, JP16, JP17, JP18, JP19, JP20, JP21, JP22, JP23, JP24: puente; Puente_alambre
JX: Conector entre placas; PinHeader_1x09_P2.54mm_Vertical
R1: 10; UnaCara_R1
R2: 10k 1%; UnaCara_R2
R3: 10k 1%; UnaCara_R3
R4: 10k; UnaCara_R4
R5: 10k; UnaCara_R5
R6: 100k; UnaCara_R6
R7: 22k 1%; UnaCara_R7
R8: 10k 1%; UnaCara_R8
R9: 10k 1%; UnaCara_R9
R10: 10k 1%; UnaCara_R10
R11: 27k 1%; UnaCara_R11
R12: 56k 1%; UnaCara_R12
R13: 10k 1%; UnaCara_R13
R14: 10k 1%; UnaCara_R14
R15: 2k7 1%; UnaCara_R15
R16: 5k6 1%; UnaCara_R16
R17: 47k 1%; UnaCara_R17
R18: 47k 1%; UnaCara_R18
R19: 47k 1%; UnaCara_R19
R20: 47k 1%; UnaCara_R20
R21: 47k 1%; UnaCara_R21
R22: 100k 1%; UnaCara_R22
R23: 100; UnaCara_R23
R24: 47k; UnaCara_R24
RV1: 10k log; UnaCara_RV1
RV2: 10k lin; UnaCara_RV2
RV3: 10k lin; UnaCara_RV3
RV4: 10k lin; UnaCara_RV4
RV5: 10k log; UnaCara_RV5
U1: MCP6004; UnaCara_U1
U2: MCP6004; UnaCara_U2

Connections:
+3.3VA: C1.1, C2.1, C4.1, C5.1, JP3.1, JP16.1, JP17.1, JX.1, R1.2, R2.1, U1.4, U2.4
+3V3: JX.8, R1.1
+5V: C3.1, J3.1, JX.9
/AGUDOS: JP20.1, R15.2, RV4.1, U2.6, U2.7
/AMP_IN: J3.3, JP19.1, RV5.2
/A_W: JP21.1, JX.4, R21.1, RV4.2
/EQ_OUT: C19.1, JP5.1, JX.6, R22.2, U2.8
/GRAVES: C11.2, JP4.1, RV2.1, U1.8, U1.9
/G_W: JP1.1, JX.5, R19.1, RV2.2
/IN_L: J1.T, R4.1
/IN_R: J1.R, R5.1
/LINEA: J2.R, J2.T, JP18.1, R23.2, R24.1, RV5.1
/MEDIOS: C15.2, JP15.1, RV3.1, U2.1, U2.2
/MED_HP: JP6.1, R11.2, R13.1, U1.13, U1.14
/M_INV: R18.2, R20.1, U2.14
/M_W: JP23.1, JP24.1, JX.7, R17.1, RV3.2
/PRE: C13.1, C17.1, JP10.1, R7.2, R9.1, U1.7
/VREF: C10.2, C12.2, C16.2, JP14.1, JX.3, R6.2, R12.2, R16.2, RV2.3, RV3.3, RV4.3, U1.1, U1.2, U2.10, U2.12
GND: C1.2, C2.2, C3.2, C4.2, C5.2, C8.2, J1.S, J2.S, J3.2, J3.4, JP2.1, JP13.1, JX.2, R3.2, R24.2, RV1.3, RV5.3, U1.11, U2.11
unnamed: C9.1, RV1.2
unnamed: C10.1, R8.2
unnamed: C11.1, R9.2, R10.1
unnamed: C13.2, C14.1, R11.1
unnamed: C15.1, JP9.1, R13.2, R14.1
unnamed: C17.2, C18.1, R15.1
unnamed: C19.2, R23.1
unnamed: R4.2, R5.2, RV1.1
unnamed: C8.1, JP12.1, R2.2, R3.1, U1.3
unnamed: C9.2, JP22.1, R6.1, U1.5
unnamed: R7.1, R8.1, U1.6
unnamed: C12.1, JP7.1, R10.2, U1.10
unnamed: C14.2, R12.1, U1.12
unnamed: C16.1, JP8.1, R14.2, U2.3
unnamed: C18.2, JP11.1, R16.1, U2.5
unnamed: R19.2, R20.2, R21.2, R22.1, U2.9
unnamed: R17.2, R18.1, U2.13
